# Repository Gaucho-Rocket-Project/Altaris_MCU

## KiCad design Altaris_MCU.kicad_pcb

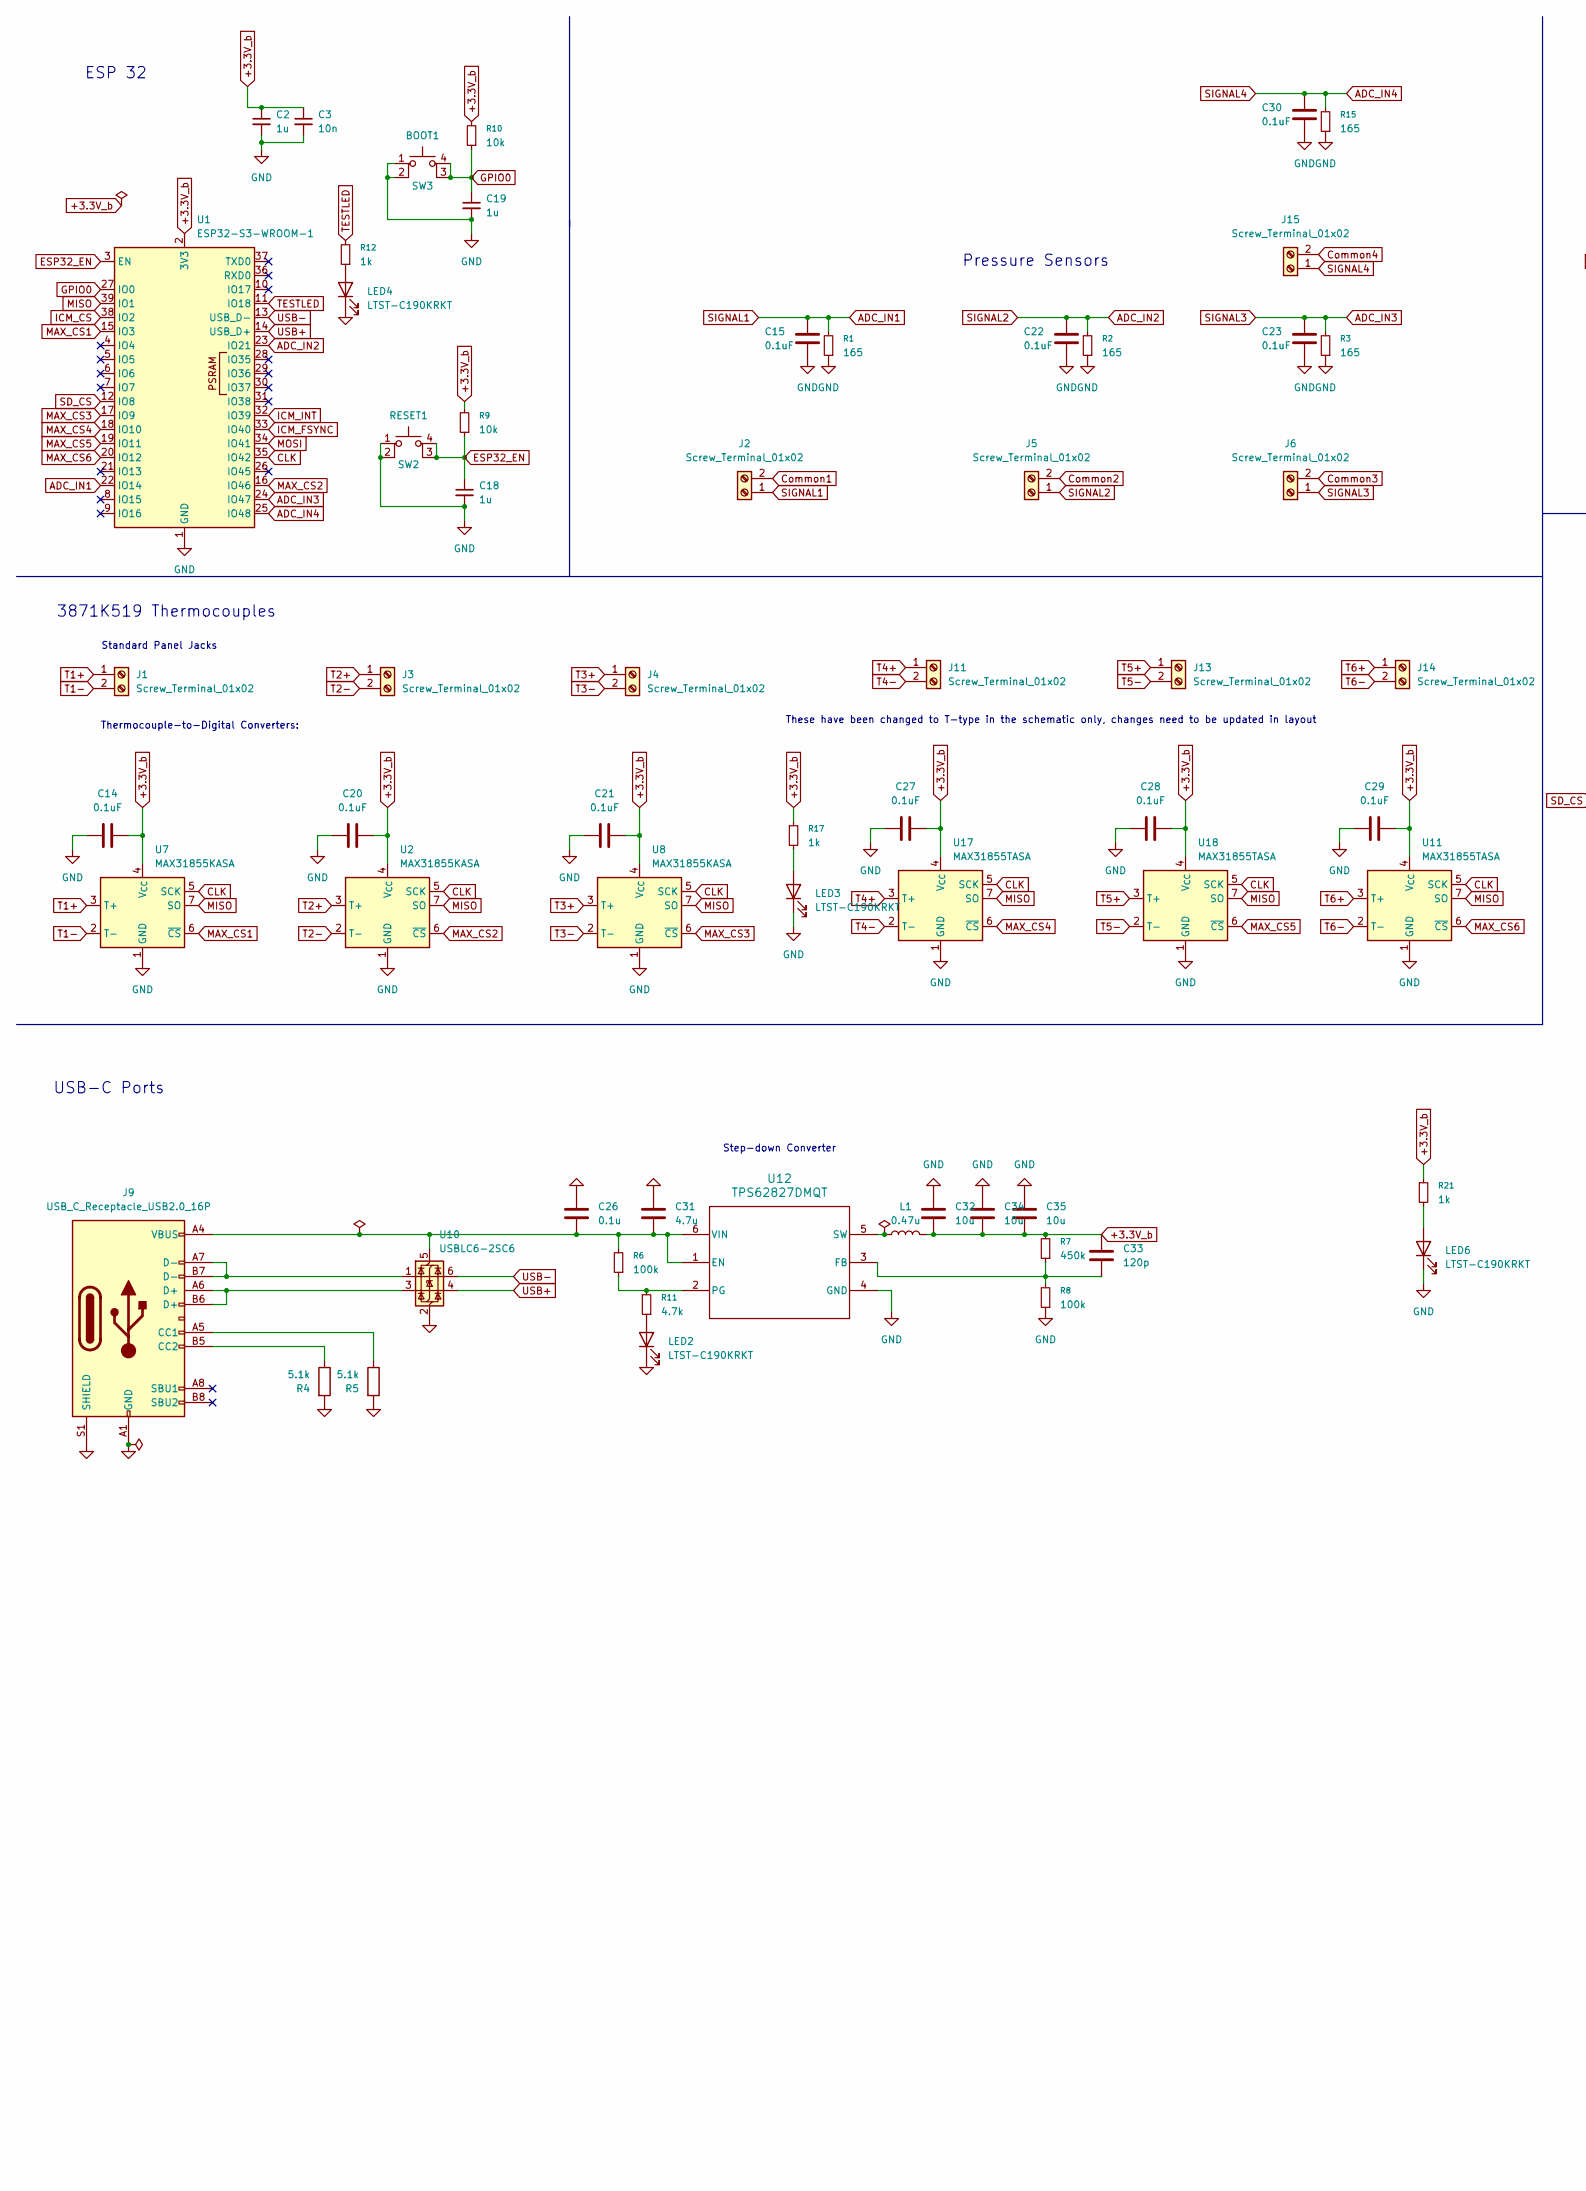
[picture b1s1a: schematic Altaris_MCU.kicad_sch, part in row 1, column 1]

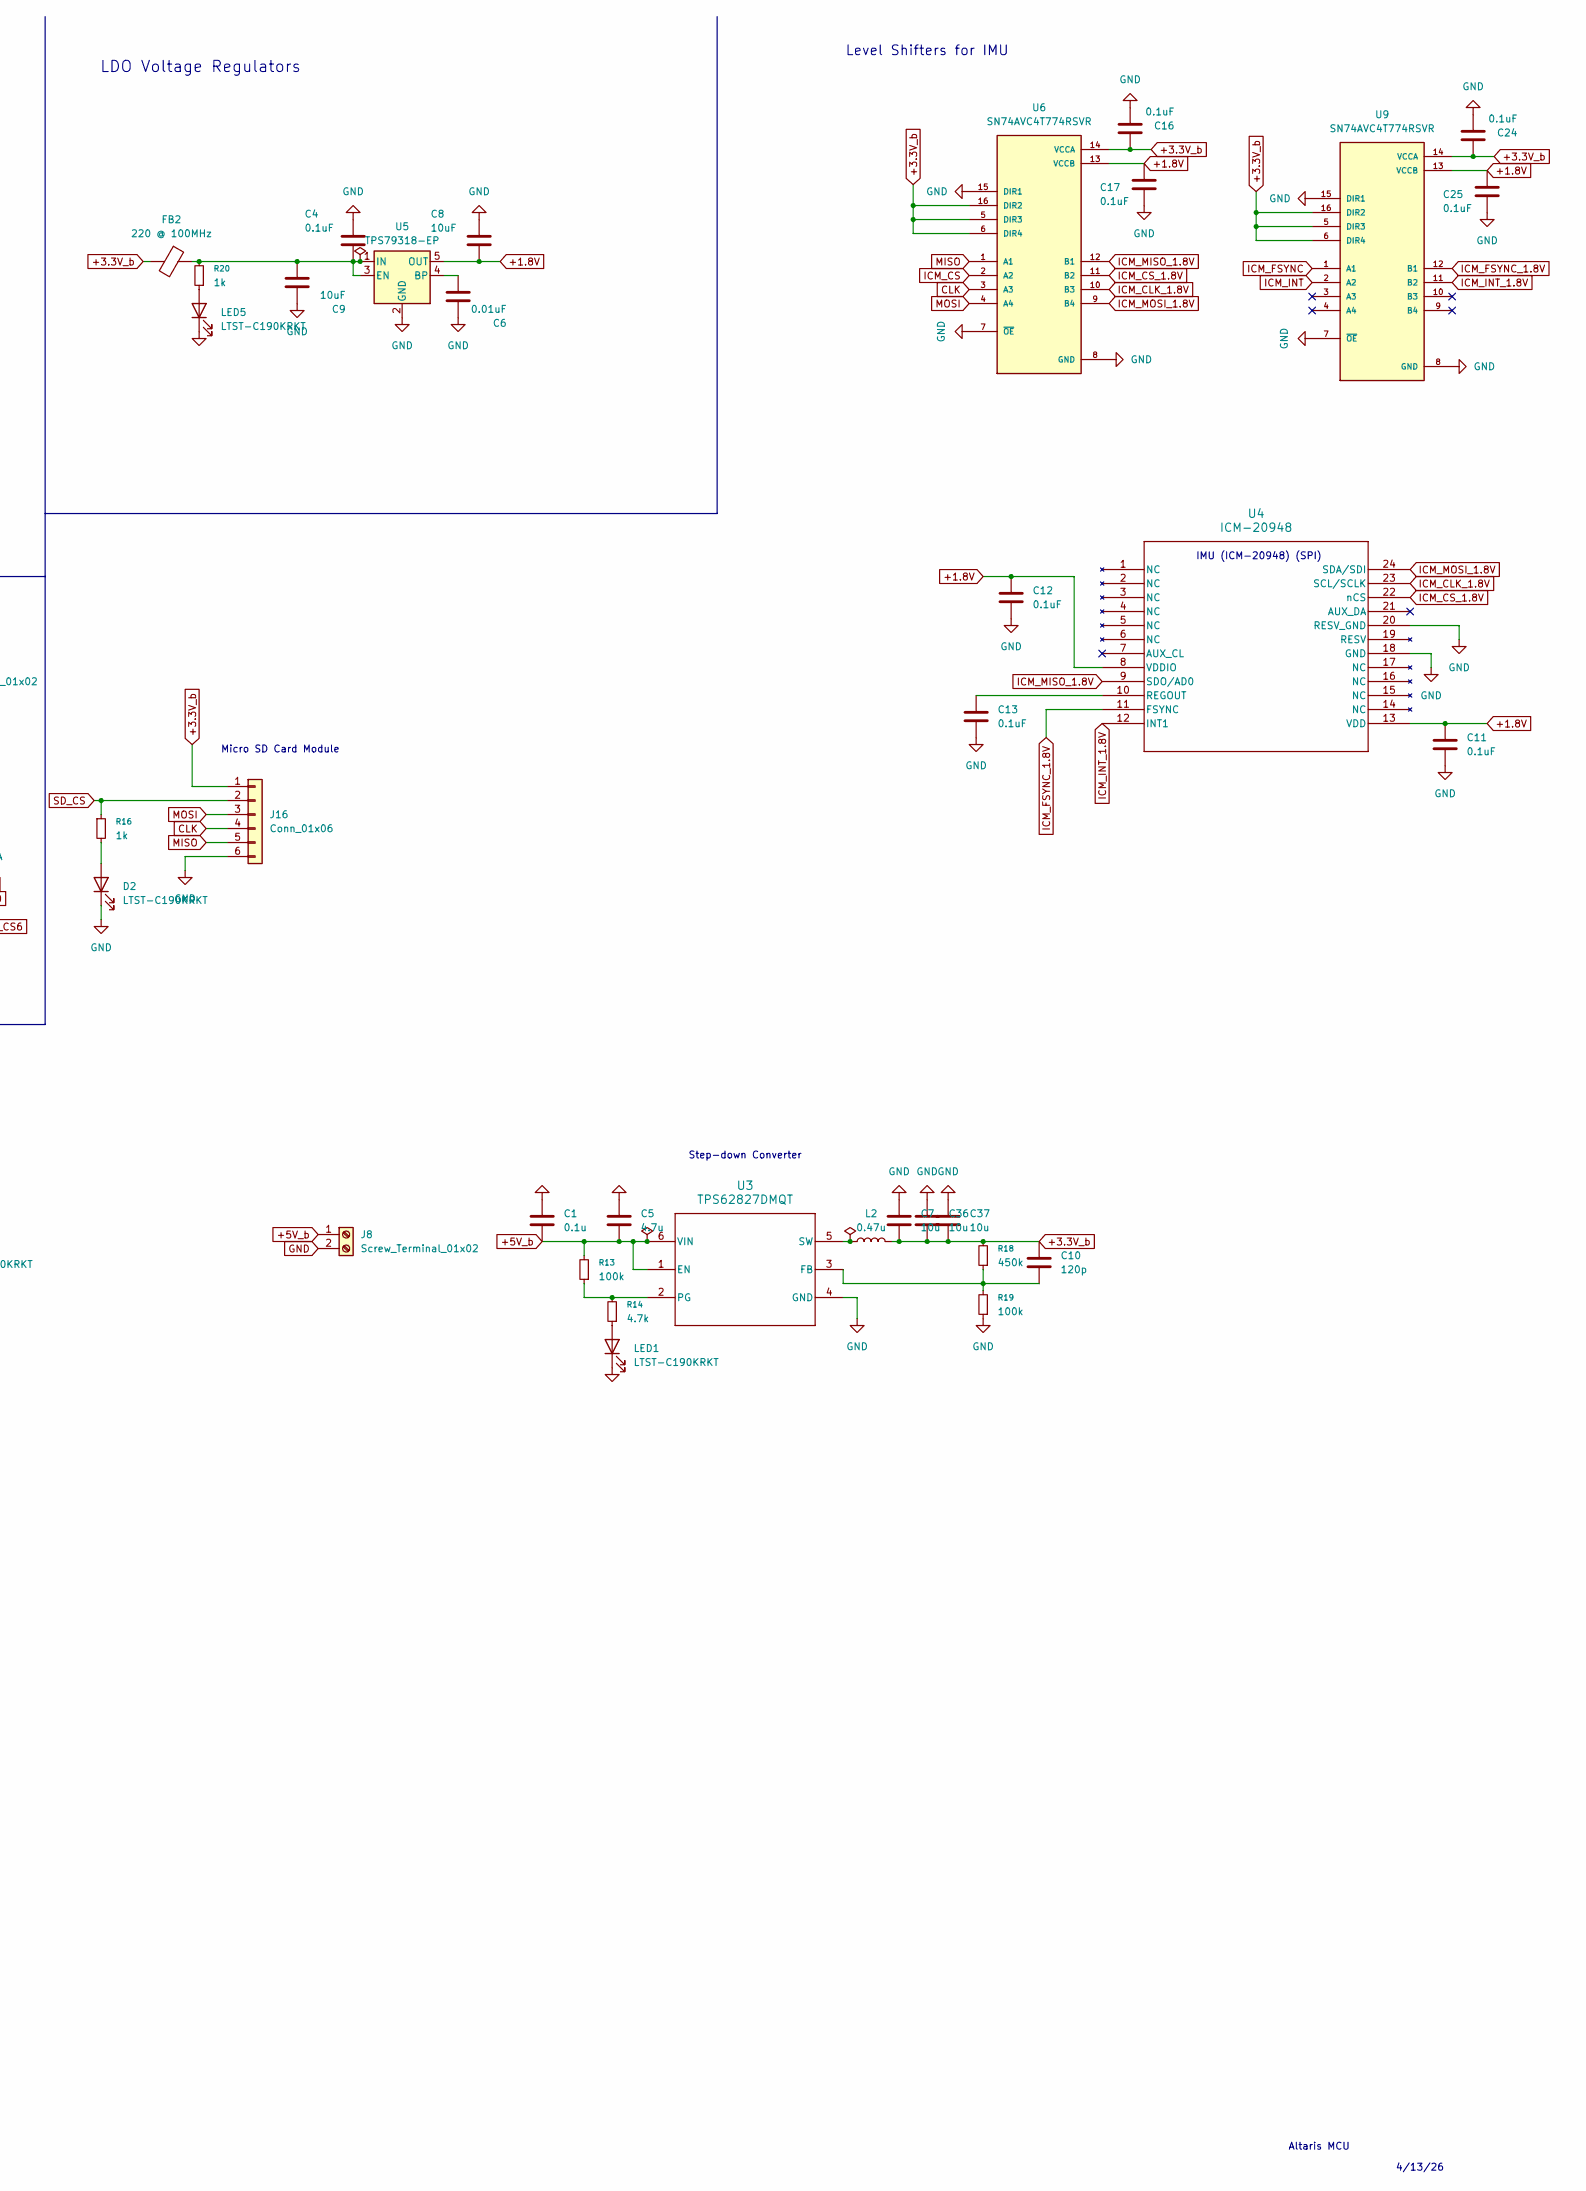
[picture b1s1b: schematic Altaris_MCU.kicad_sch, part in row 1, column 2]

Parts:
C1, C26: 0.1u; C_0201_0603Metric; Manufacturer Part Number CL05B104KO5NNNC; LCSC C1525
C2, C18, C19: 1u; C_0402_1005Metric
C3: 10n; C_0402_1005Metric
C4, C15, C22, C23, C30: 0.1uF; C_0805_2012Metric_Pad1.18x1.45mm_HandSolder; LCSC C28233
C5, C31: 4.7u; C_0201_0603Metric; Manufacturer Part Number CL05B104KO5NNNC; LCSC C1525
C6: 0.01uF; C_0805_2012Metric_Pad1.18x1.45mm_HandSolder; LCSC C28233
C7, C32, C34, C35, C36, C37: 10u; C_0201_0603Metric; Manufacturer Part Number CL05B104KO5NNNC; LCSC C1525
C8: 10uF; C_0805_2012Metric_Pad1.18x1.45mm_HandSolder; LCSC C15850
C9: 10uF; C_0805_2012Metric_Pad1.18x1.45mm_HandSolder; LCSC C28233
C10, C33: 120p; C_0201_0603Metric; Manufacturer Part Number CL05B104KO5NNNC; LCSC C1525
C11, C12, C13, C14, C16, C17, C20, C21, C24, C25, C27, C28, C29: 0.1uF; C_0402_1005Metric_Pad0.74x0.62mm_HandSolder
D2: LTST-C190KRKT; LED_0603_1608Metric
FB2: 220 @ 100MHz; L_0402_1005Metric_Pad0.77x0.64mm_HandSolder
J1, J2, J3, J4, J5, J6, J8, J11, J13, J14, J15: Screw_Terminal_01x02; TerminalBlock_MaiXu_MX126-5.0-02P_1x02_P5.00mm
J9: USB_C_Receptacle_USB2.0_16P; USB_C_Receptacle_HRO_TYPE-C-31-M-12; Manufacturer Part Number TYPE-C-31-M-12; LCSC C165948
J16: Conn_01x06; PinHeader_1x06_P2.54mm_Vertical
L1, L2: 0.47u; IND_XFL4015_COC
LED1, LED2, LED3, LED4, LED5, LED6: LTST-C190KRKT; LED_0603_1608Metric
R1, R2, R3, R15: 165; R_0402_1005Metric
R4, R5: 5.1k; R_0402_1005Metric; Manufacturer Part Number 0402WGF5101TCE; LCSC C25905
R6, R8, R13, R19: 100k; R_0402_1005Metric
R7, R18: 450k; R_0402_1005Metric
R9, R10: 10k; R_0402_1005Metric
R11, R14: 4.7k; R_0402_1005Metric
R12, R20: 1k; R_0402_1005Metric
R16, R17, R21: 1k; R_0603_1608Metric
SW2: RESET1; SW_MEC_5GSH9
SW3: BOOT1; SW_MEC_5GSH9
U1: ESP32-S3-WROOM-1
U2, U7, U8: MAX31855KASA; SOIC-8_3.9x4.9mm_P1.27mm
U3, U12: TPS62827DMQT; DMQ0006A
U4: ICM-20948; QFN24_3X3X0P9_IVS; LCSC C726001
U5: TPS79318-EP; SOT-23-5; LCSC C7102
U6, U9: SN74AVC4T774RSVR; RSV0016A; PARTREV E
U10: USBLC6-2SC6; SOT-23-6
U11, U17, U18: MAX31855TASA; SOIC-8_3.9x4.9mm_P1.27mm

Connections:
+1.8V: C8.2, C11.1, C12.1, C17.1, C25.1, U4.8 (VDDIO), U4.13 (VDD), U5.5 (OUT), U6.13 (VCCB), U9.13 (VCCB)
+3.3V_b: C2.1, C3.1, C7.1, C10.1, C14.1, C16.1, C20.1, C21.1, C24.1, C27.1, C28.1, C29.1, C32.1, C33.1, C34.1, C35.1, C36.1, C37.1, FB2.2, J16.1, L1.2, L2.2, R7.2, R9.2, R10.2, R17.1, R18.2, R21.1, U1.2 (3V3), U2.4 (V_{CC}), U6.5 (DIR3), U6.6 (DIR4), U6.14 (VCCA), U6.16 (DIR2), U7.4 (V_{CC}), U8.4 (V_{CC}), U9.5 (DIR3), U9.6 (DIR4), U9.14 (VCCA), U9.16 (DIR2), U11.4 (V_{CC}), U17.4 (V_{CC}), U18.4 (V_{CC})
+5V_b: C1.2, C5.2, J8.1, R13.2, U3.1 (EN), U3.6 (VIN)
ADC_IN1: C15.1, J2.1, R1.2, U1.22 (IO14)
ADC_IN2: C22.1, J5.1, R2.2, U1.23 (IO21)
ADC_IN3: C23.1, J6.1, R3.2, U1.24 (IO47)
ADC_IN4: C30.1, J15.1, R15.2, U1.25 (IO48)
CLK: J16.4, U1.35 (IO42), U2.5 (SCK), U6.3 (A3), U7.5 (SCK), U8.5 (SCK), U11.5 (SCK), U17.5 (SCK), U18.5 (SCK)
Common1: J2.2
Common2: J5.2
Common3: J6.2
Common4: J15.2
ESP32_EN: C18.1, R9.1, SW2.3 (K), SW2.4 (A), U1.3 (EN)
GND: C1.1, C2.2, C3.2, C4.1, C5.1, C6.1, C7.2, C8.1, C9.1, C11.2, C12.2, C13.2, C14.2, C15.2, C16.2, C17.2, C18.2, C19.2, C20.2, C21.2, C22.2, C23.2, C24.2, C25.2, C26.1, C27.2, C28.2, C29.2, C30.2, C31.1, C32.2, C34.2, C35.2, C36.2, C37.2, D2.1 (K), J8.2, J9.A1 (GND), J9.A12 (GND), J9.B1 (GND), J9.B12 (GND), J9.S1 (SHIELD), J16.6, LED1.1 (K), LED2.1 (K), LED3.1 (K), LED4.1 (K), LED5.1 (K), LED6.1 (K), R1.1, R2.1, R3.1, R4.2, R5.2, R8.1, R15.1, R19.1, SW2.1, SW2.2, SW3.1, SW3.2, U1.1 (GND), U1.40 (GND), U1.41 (GND), U2.1 (GND), U3.4 (GND), U4.18 (GND), U4.20 (RESV_GND), U5.2 (GND), U6.7 (~OE), U6.8 (GND), U6.15 (DIR1), U7.1 (GND), U8.1 (GND), U9.7 (~OE), U9.8 (GND), U9.15 (DIR1), U10.2 (GND), U11.1 (GND), U12.4 (GND), U17.1 (GND), U18.1 (GND)
GPIO0: C19.1, R10.1, SW3.3 (K), SW3.4 (A), U1.27 (IO0)
ICM_CLK_1.8V: U4.23 (SCL/SCLK), U6.10 (B3)
ICM_CS: U1.38 (IO2), U6.2 (A2)
ICM_CS_1.8V: U4.22 (nCS), U6.11 (B2)
ICM_FSYNC: U1.33 (IO40), U9.1 (A1)
ICM_FSYNC_1.8V: U4.11 (FSYNC), U9.12 (B1)
ICM_INT: U1.32 (IO39), U9.2 (A2)
ICM_INT_1.8V: U4.12 (INT1), U9.11 (B2)
ICM_MISO_1.8V: U4.9 (SDO/AD0), U6.12 (B1)
ICM_MOSI_1.8V: U4.24 (SDA/SDI), U6.9 (B4)
MAX_CS1: U1.15 (IO3), U7.6 (~CS)
MAX_CS2: U1.16 (IO46), U2.6 (~CS)
MAX_CS3: U1.17 (IO9), U8.6 (~CS)
MAX_CS4: U1.18 (IO10), U17.6 (~CS)
MAX_CS5: U1.19 (IO11), U18.6 (~CS)
MAX_CS6: U1.20 (IO12), U11.6 (~CS)
MISO: J16.5, U1.39 (IO1), U2.7 (SO), U6.1 (A1), U7.7 (SO), U8.7 (SO), U11.7 (SO), U17.7 (SO), U18.7 (SO)
MOSI: J16.3, U1.34 (IO41), U6.4 (A4)
unnamed: D2.2 (A), R16.2
unnamed: J9.A5 (CC1), R5.1
unnamed: J9.B5 (CC2), R4.1
unnamed: J9.A6 (D+), J9.B6 (D+), U10.3 (I/O2)
unnamed: J9.A7 (D-), J9.B7 (D-), U10.1 (I/O1)
unnamed: LED1.2 (A), R14.1
unnamed: LED2.2 (A), R11.1
unnamed: LED3.2 (A), R17.2
unnamed: LED4.2 (A), R12.1
unnamed: LED5.2 (A), R20.1
unnamed: LED6.2 (A), R21.2
unnamed: C10.2, R18.1, R19.2, U3.3 (FB)
unnamed: R13.1, R14.2, U3.2 (PG)
unnamed: L2.1, U3.5 (SW)
unnamed: C13.1, U4.10 (REGOUT)
unnamed: C6.2, U5.4 (BP)
unnamed: C4.2, C9.2, FB2.1, R20.2, U5.1 (IN), U5.3 (EN)
unnamed: C26.2, C31.2, J9.A4 (VBUS), J9.A9 (VBUS), J9.B4 (VBUS), J9.B9 (VBUS), R6.2, U10.5 (VBUS), U12.1 (EN), U12.6 (VIN)
unnamed: C33.2, R7.1, R8.2, U12.3 (FB)
unnamed: R6.1, R11.2, U12.2 (PG)
unnamed: L1.1, U12.5 (SW)
SD_CS: J16.2, R16.1, U1.12 (IO8)
T1+: J1.1, U7.3 (T+)
T1-: J1.2, U7.2 (T-)
T2+: J3.1, U2.3 (T+)
T2-: J3.2, U2.2 (T-)
T3+: J4.1, U8.3 (T+)
T3-: J4.2, U8.2 (T-)
T4+: J11.1, U17.3 (T+)
T4-: J11.2, U17.2 (T-)
T5+: J13.1, U18.3 (T+)
T5-: J13.2, U18.2 (T-)
T6+: J14.1, U11.3 (T+)
T6-: J14.2, U11.2 (T-)
TESTLED: R12.2, U1.11 (IO18)
USB+: U1.14 (USB_D+), U10.4 (I/O2)
USB-: U1.13 (USB_D-), U10.6 (I/O1)

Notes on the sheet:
Altaris MCU
ESP 32
Level Shifters for IMU
LDO Voltage Regulators
4/13/26
USB-C Ports
Standard Panel Jacks
These have been changed to T-type in the schematic only, changes need to be updated in layout
Micro SD Card Module
Thermocouple-to-Digital Converters:
Step-down Converter
3871K519 Thermocouples
Pressure Sensors
IMU (ICM-20948) (SPI)

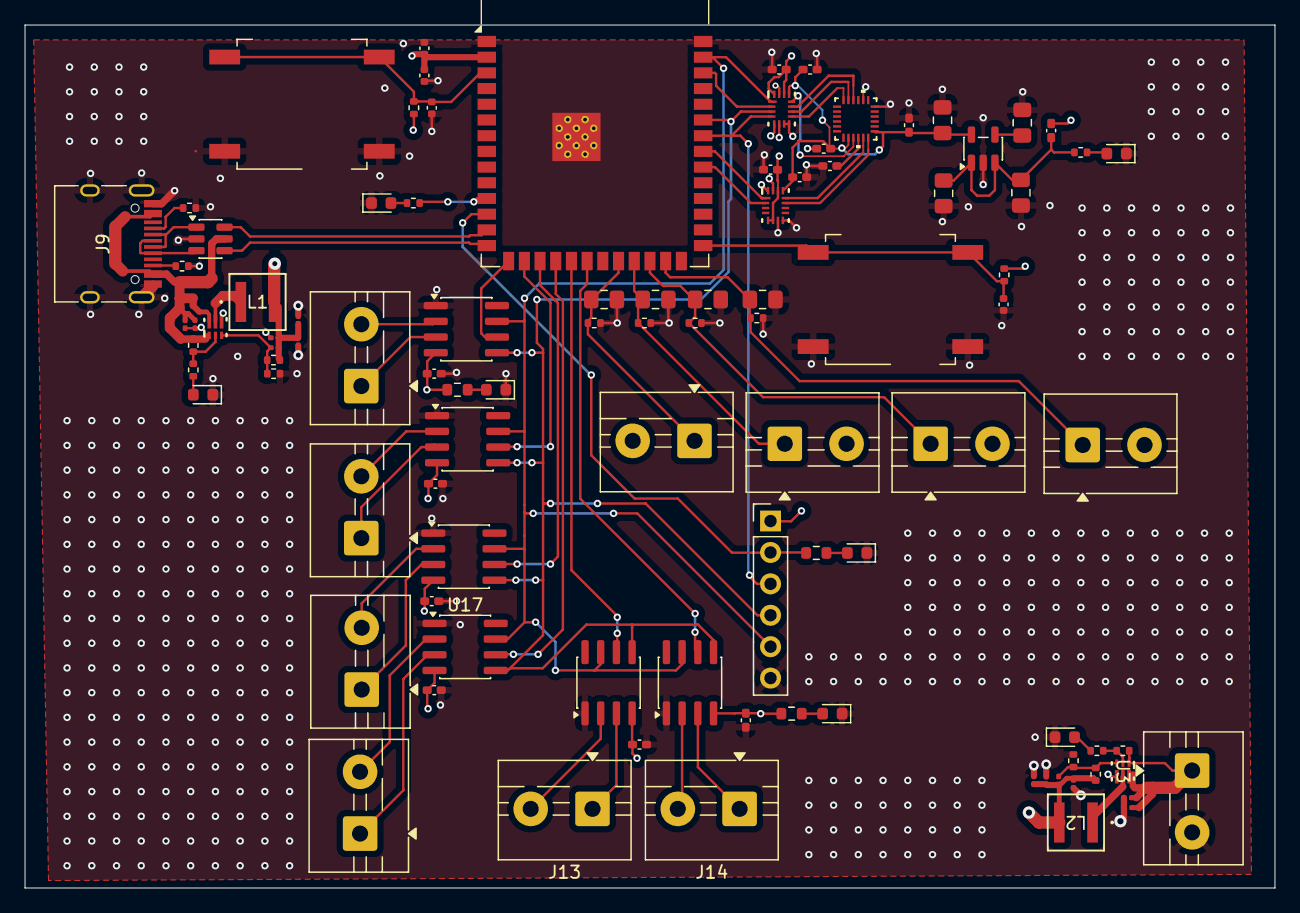
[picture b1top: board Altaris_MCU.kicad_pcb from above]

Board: 4 copper layers, 101.1 x 69.8 mm, 97 parts (0 on the bottom side), 65 nets.

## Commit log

2026-04-09 Added more sensors and removed old labels
2026-04-12 Added USB-C to Schematic and PCB Layout
2026-04-12 Added Buck Converter to Schematic
    USB-C BUS(5V) -> BUCK -> 3.3V -> (Voltage regulator to get 1.8V?)
2026-04-14 added second USB port, labels, organize
2026-04-15 Swapped LDO for Buck and added some test LED's
2026-04-16 Moved USB-C, Routed Buck converter output to LDO, Removed an LDO on PCB, Added another Thermocouple sensor
2026-04-16 Changed to 4 layer board, moved USB-C, rerouted
2026-04-20 added top gnd plane and stitching vias
2026-04-21 Fixed second USB port wiring, changed to screw terminals
2026-04-21 Small changes to USB ports, ran ERC
2026-04-22 added stitching vias, added power screw terminals
2026-04-23 added two screw terminal and MAX for extra thermocouples
2026-04-23 Added micro SD card module w/ library
2026-04-25 Footprints
2026-04-25 Symbols
2026-04-26 Added header for MicroSD module to layout, changed 3 thermocouple MAX to T type in schematic only
2026-04-26 minor edits to layout and schematic
2026-04-26 fixed an error with netting
2026-04-26 added vias, tweaked sd_cs via/tracing
2026-04-26 re-commmit from prev, forgot to save
2026-04-28 added another pressure sensor measuring
2026-04-29 added led to thermocouple power lines in schematic
2026-04-29 Altaris_MCU.kicad_pcb
2026-04-29 Cleaned up schematic, added 5V screw terminal and 3.3V buck converter, added some test led, ran DRC and fixed connections
2026-04-29 pcb edit
2026-04-29 finalized pcb
2026-04-29 final pcb
2026-04-29 pcb final 1
2026-04-30 edited capcitors
2026-05-18 chore: sync ci configuration
